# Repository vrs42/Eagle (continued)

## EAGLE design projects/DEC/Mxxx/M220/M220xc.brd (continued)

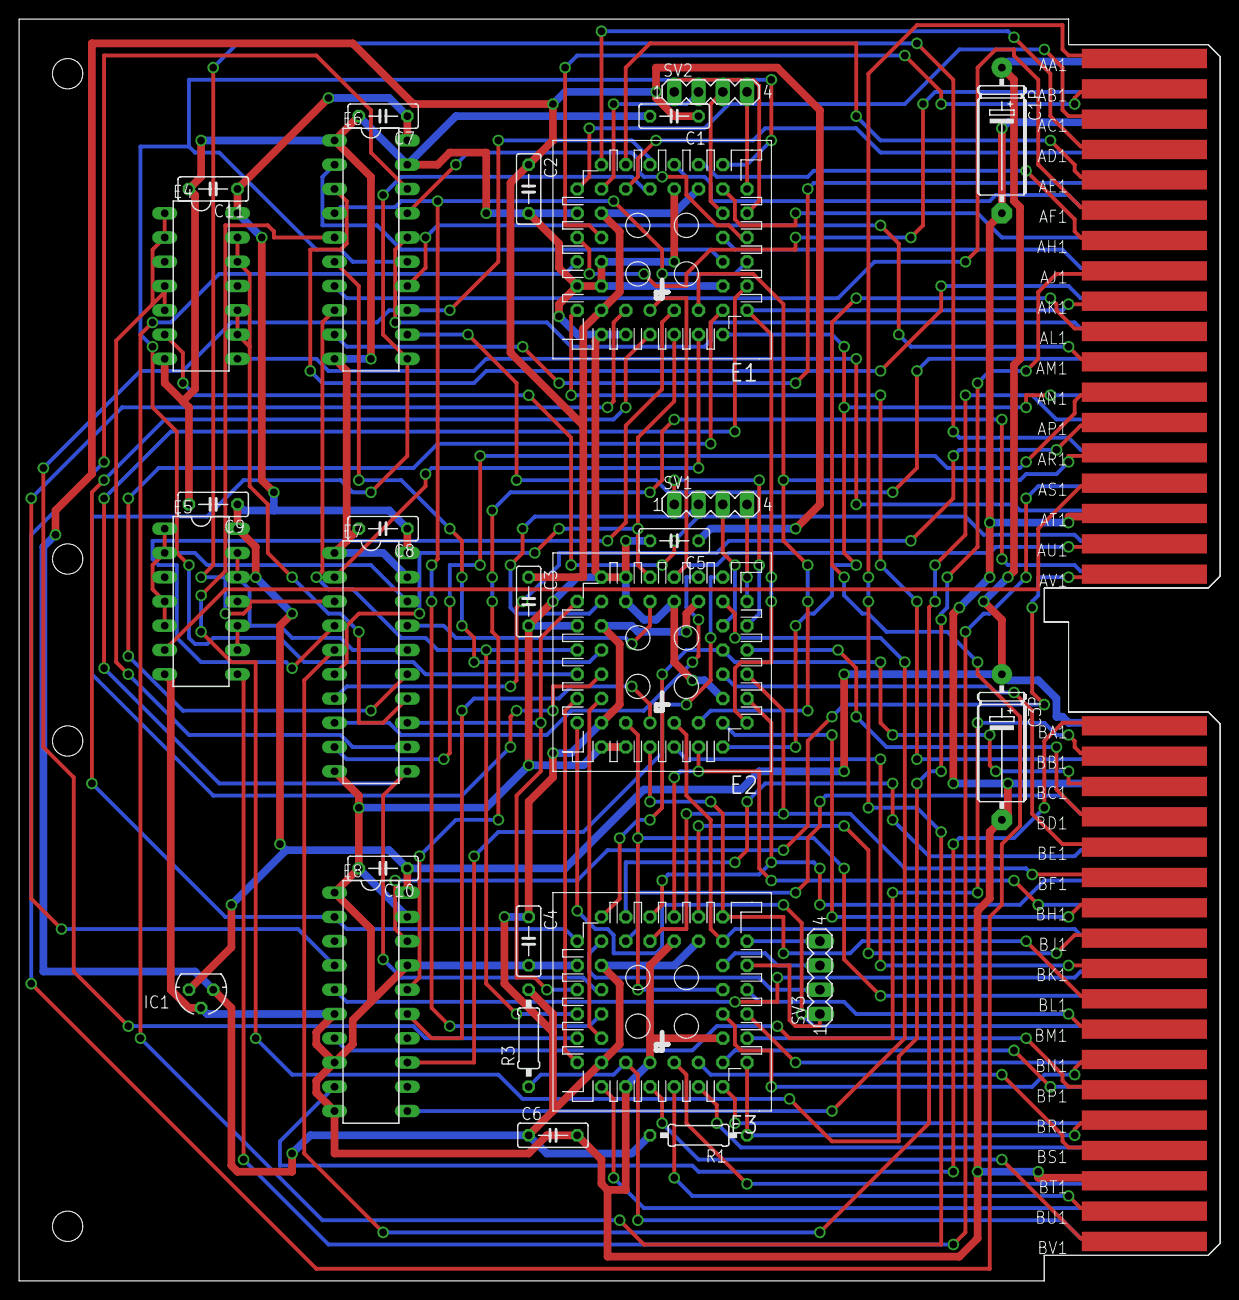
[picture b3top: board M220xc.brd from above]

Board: 2 copper layers, 125.7 x 132.1 mm, 29 parts (0 on the bottom side), 108 nets.
